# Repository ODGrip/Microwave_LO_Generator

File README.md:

# Microwave_LO_Generator
23.3 GHz - 26.3 GHz LO generator

View on CADLAB.io: https://cadlab.io/projects/microwavelogenerator

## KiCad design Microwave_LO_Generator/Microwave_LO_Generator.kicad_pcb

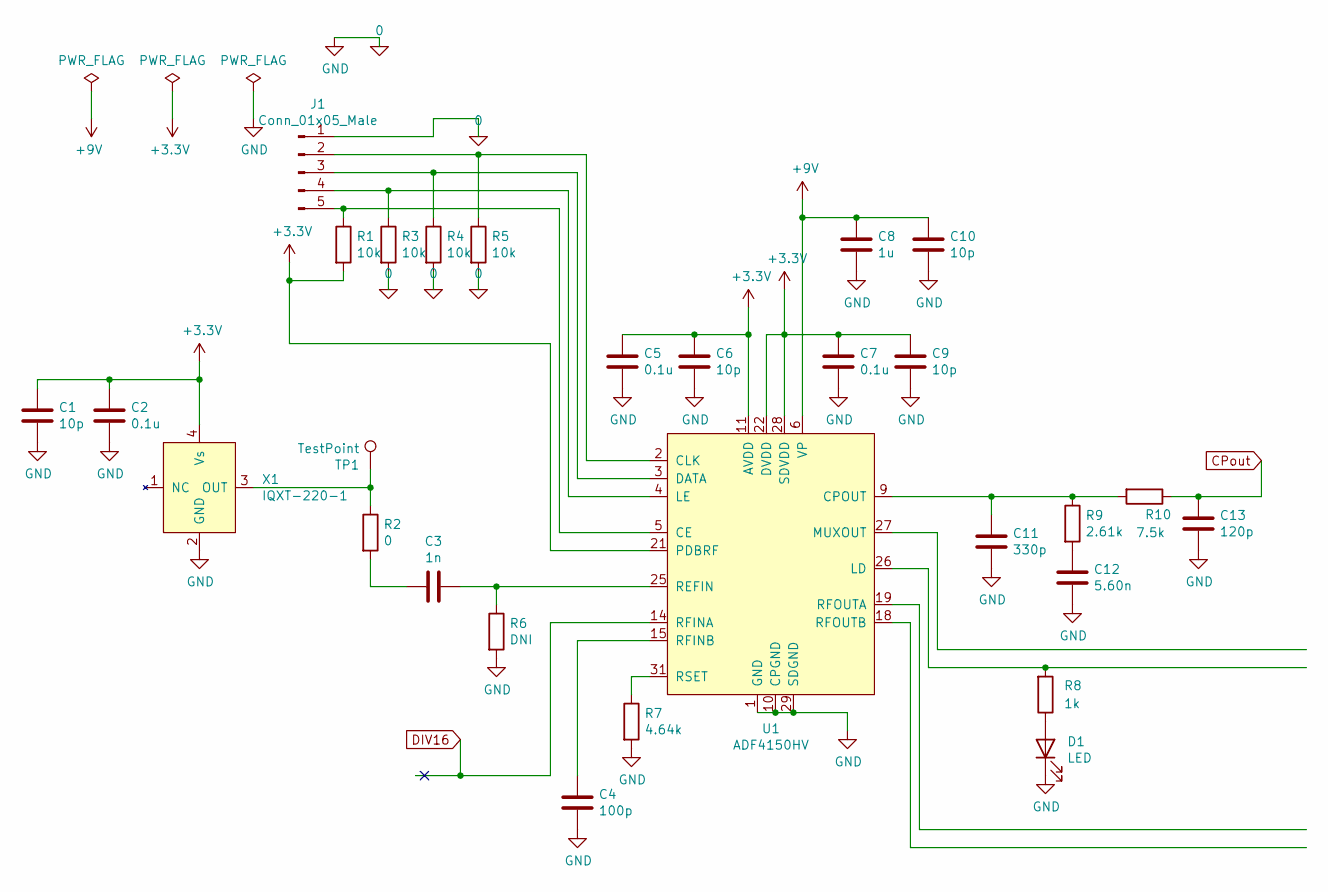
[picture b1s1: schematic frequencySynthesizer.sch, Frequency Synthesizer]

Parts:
C1, C6, C9, C10: 10p; C_0402_1005Metric_Pad0.74x0.62mm_HandSolder
C2, C5, C7: 0.1u; C_0402_1005Metric_Pad0.74x0.62mm_HandSolder
C3: 1n; C_0402_1005Metric_Pad0.74x0.62mm_HandSolder
C4: 100p; C_0402_1005Metric_Pad0.74x0.62mm_HandSolder
C8: 1u; C_0402_1005Metric_Pad0.74x0.62mm_HandSolder
C11: 330p; C_0402_1005Metric_Pad0.74x0.62mm_HandSolder
C12: 5.60n; C_0402_1005Metric_Pad0.74x0.62mm_HandSolder
C13: 120p; C_0402_1005Metric_Pad0.74x0.62mm_HandSolder
D1: LED; LED_0805_2012Metric_Pad1.15x1.40mm_HandSolder
J1: Conn_01x05_Male; PinHeader_1x05_P2.54mm_Vertical
R1, R3, R4, R5: 10k; R_0402_1005Metric_Pad0.72x0.64mm_HandSolder
R2: 0; R_0402_1005Metric_Pad0.72x0.64mm_HandSolder
R6: DNI; R_0402_1005Metric_Pad0.72x0.64mm_HandSolder
R7: 4.64k; R_0402_1005Metric_Pad0.72x0.64mm_HandSolder
R8: 1k; R_0402_1005Metric_Pad0.72x0.64mm_HandSolder
R9: 2.61k; R_0402_1005Metric_Pad0.72x0.64mm_HandSolder
R10: 7.5k; R_0402_1005Metric_Pad0.72x0.64mm_HandSolder
TP1: TestPoint; TestPoint_Loop_D2.60mm_Drill1.6mm_Beaded
U1: ADF4150HV; LFCSP-32-1EP_5x5mm_P0.5mm_mod
X1: IQXT-220-1; Oscillator_SMD_Abracon_ASE-4Pin_3.2x2.5mm_HandSoldering

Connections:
0: C1.1, C2.1, C4.1, C5.1, C6.1, C7.1, C8.1, C9.1, C10.1, C11.1, C12.1, C13.1, D1.1 (K), J1.1, R3.2, R4.2, R5.2, R6.2, R7.2, U1.1 (GND), U1.7 (GND), U1.8 (GND), U1.10 (CPGND), U1.12 (GND), U1.16 (GND), U1.17 (GND), U1.23 (GND), U1.24 (GND), U1.29 (SDGND), U1.30 (GND), U1.32 (GND), X1.2 (GND); also elsewhere on the board
+3V3: C1.2, C2.2, C5.2, C6.2, C7.2, C9.2, R1.2, U1.11 (AVDD), U1.13 (AVDD), U1.20 (AVDD), U1.21 (PDBRF), U1.22 (DVDD), U1.28 (SDVDD), X1.4 (Vs); also elsewhere on the board
+9V: C8.2, C10.2, U1.6 (VP); also elsewhere on the board
CPout: C13.2, R10.1; also elsewhere on the board
DIV16: U1.14 (RFINA); also elsewhere on the board
unnamed: C3.1, R6.1, U1.25 (REFIN)
unnamed: C3.2, R2.2
unnamed: C4.2, U1.15 (RFINB)
unnamed: C11.2, R9.1, R10.2, U1.9 (CPOUT)
unnamed: C12.2, R9.2
unnamed: D1.2 (A), R8.1
unnamed: J1.2, R5.1, U1.2 (CLK)
unnamed: J1.3, R4.1, U1.3 (DATA)
unnamed: J1.4, R3.1, U1.4 (LE)
unnamed: J1.5, R1.1, U1.5 (CE)
unnamed: R2.1, TP1.1, X1.3 (OUT)
unnamed: R7.1, U1.31 (RSET)
unnamed: R8.2, U1.26 (LD)

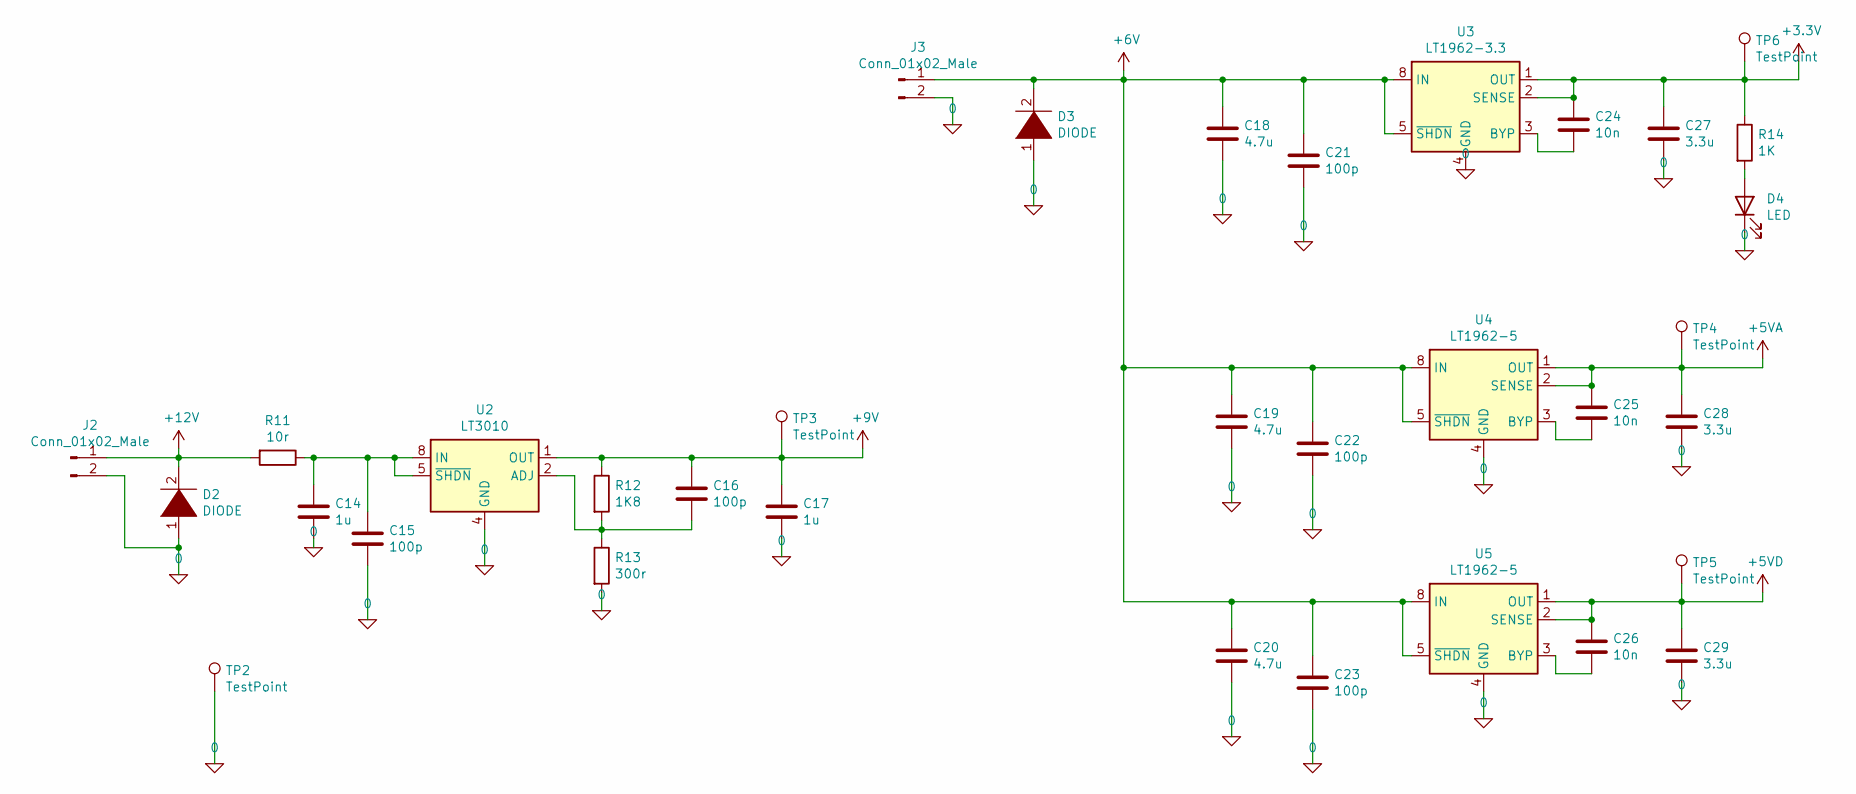
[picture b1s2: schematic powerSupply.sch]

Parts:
C14, C17: 1u; C_0402_1005Metric_Pad0.74x0.62mm_HandSolder
C15, C16, C21, C22, C23: 100p; C_0402_1005Metric_Pad0.74x0.62mm_HandSolder
C18, C19, C20: 4.7u; C_0402_1005Metric_Pad0.74x0.62mm_HandSolder
C24, C25, C26: 10n; C_0402_1005Metric_Pad0.74x0.62mm_HandSolder
C27, C28, C29: 3.3u; C_0402_1005Metric_Pad0.74x0.62mm_HandSolder
D2, D3: DIODE; D_MELF
D4: LED; LED_0805_2012Metric_Pad1.15x1.40mm_HandSolder
J2, J3: Conn_01x02_Male; PinHeader_1x02_P2.54mm_Vertical
R11: 10r; R_0402_1005Metric_Pad0.72x0.64mm_HandSolder
R12: 1K8; R_0402_1005Metric_Pad0.72x0.64mm_HandSolder
R13: 300r; R_0402_1005Metric_Pad0.72x0.64mm_HandSolder
R14: 1K; R_0402_1005Metric_Pad0.72x0.64mm_HandSolder
TP2, TP3, TP4, TP5, TP6: TestPoint; TestPoint_Loop_D2.60mm_Drill1.6mm_Beaded
U2: LT3010; MSOP-8-1EP_3x3mm_P0.65mm_EP1.68x1.88mm
U3: LT1962-3.3; MSOP-8_3x3mm_P0.65mm
U4, U5: LT1962-5; MSOP-8_3x3mm_P0.65mm

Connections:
0: C14.1, C15.1, C17.1, C18.1, C19.1, C20.1, C21.1, C22.1, C23.1, C27.1, C28.1, C29.1, D2.1 (K), D3.1 (K), D4.1 (K), J2.2, J3.2, R13.2, TP2.1, U2.4 (GND), U2.9 (GND), U3.4 (GND), U4.4 (GND), U5.4 (GND); also elsewhere on the board
+3V3: C24.2, C27.2, R14.1, TP6.1, U3.1 (OUT), U3.2 (SENSE); also elsewhere on the board
+5VA: C25.2, C28.2, TP4.1, U4.1 (OUT), U4.2 (SENSE); also elsewhere on the board
+5VD: C26.2, C29.2, TP5.1, U5.1 (OUT), U5.2 (SENSE); also elsewhere on the board
+6V: C18.2, C19.2, C20.2, C21.2, C22.2, C23.2, D3.2 (A), J3.1, U3.5 (~SHDN), U3.8 (IN), U4.5 (~SHDN), U4.8 (IN), U5.5 (~SHDN), U5.8 (IN)
+9V: C16.2, C17.2, R12.1, TP3.1, U2.1 (OUT); also elsewhere on the board
+12V: D2.2 (A), J2.1, R11.2
unnamed: C14.2, C15.2, R11.1, U2.5 (~SHDN), U2.8 (IN)
unnamed: C16.1, R12.2, R13.1, U2.2 (ADJ)
unnamed: C24.1, U3.3 (BYP)
unnamed: C25.1, U4.3 (BYP)
unnamed: C26.1, U5.3 (BYP)
unnamed: D4.2 (A), R14.2

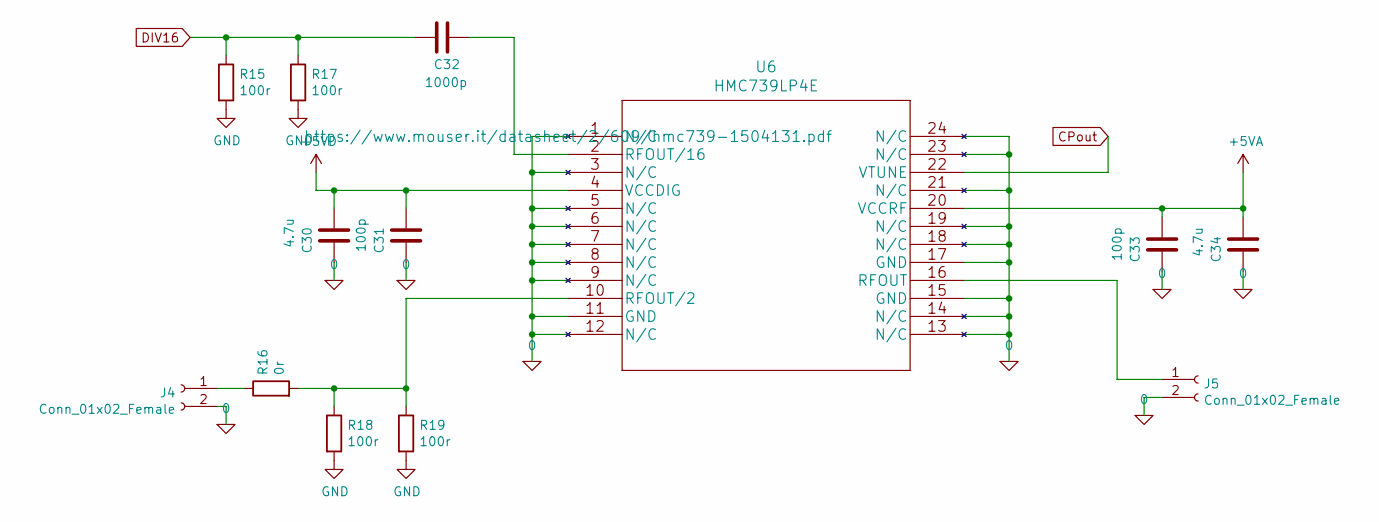
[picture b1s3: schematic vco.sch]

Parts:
C30, C34: 4.7u; C_0402_1005Metric_Pad0.74x0.62mm_HandSolder
C31, C33: 100p; C_0402_1005Metric_Pad0.74x0.62mm_HandSolder
C32: 1000p; C_0201_0603Metric_Pad0.64x0.40mm_HandSolder
J4, J5: Conn_01x02_Female; Connettore_largo
R15, R17, R18, R19: 100r; R_0201_0603_HandSolder_mod
R16: 0r; R_0201_0603_HandSolder_mod
U6: HMC739LP4E; QFN-24-1EP_4x4mm_P0.5mm_EP2.7x2.7mm_ThermalVias_mod

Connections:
0: C30.2, C31.2, C33.2, C34.2, J4.2, J5.2, R15.2, R17.2, R18.2, R19.2, U6.1 (N/C), U6.3 (N/C), U6.5 (N/C), U6.6 (N/C), U6.7 (N/C), U6.8 (N/C), U6.9 (N/C), U6.11 (GND), U6.12 (N/C), U6.13 (N/C), U6.14 (N/C), U6.15 (GND), U6.17 (GND), U6.18 (N/C), U6.19 (N/C), U6.21 (N/C), U6.23 (N/C), U6.24 (N/C); also elsewhere on the board
+5VA: C33.1, C34.1, U6.20 (VCCRF); also elsewhere on the board
+5VD: C30.1, C31.1, U6.4 (VCCDIG); also elsewhere on the board
CPout: U6.22 (VTUNE); also elsewhere on the board
DIV16: C32.1, R15.1, R17.1; also elsewhere on the board
unnamed: C32.2, U6.2 (RFOUT/16)
unnamed: J4.1, R16.1
unnamed: J5.1, U6.16 (RFOUT)
unnamed: R16.2, R18.1, R19.1, U6.10 (RFOUT/2)

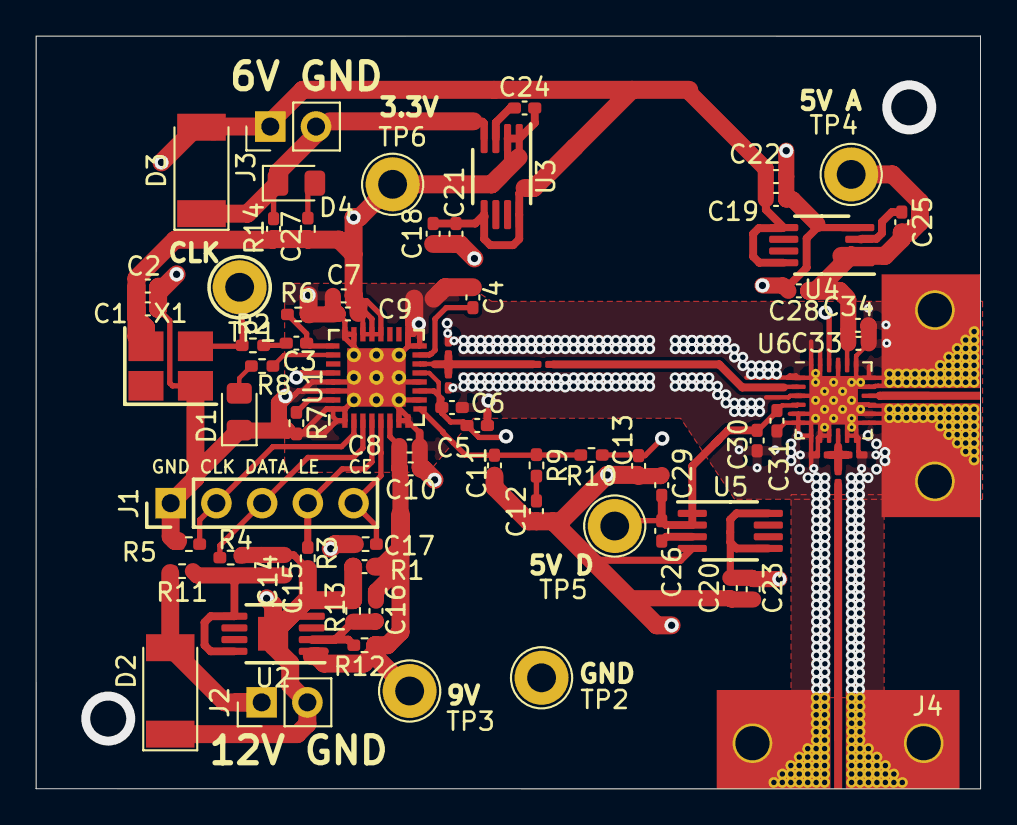
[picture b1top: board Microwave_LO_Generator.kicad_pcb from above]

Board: 4 copper layers, 52.5 x 41.8 mm, 75 parts (0 on the bottom side), 32 nets.

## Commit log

2020-11-24 First commit
    Initial setup
2020-11-25 add vco
2020-11-25 Update and fix
2020-11-25 add CADLAB.io link
2020-11-26 Update PCB
2020-11-27 Add connector pcb model
2020-12-03 Power Supply update
2020-12-04 Add RF/2
2020-12-05 A lot of change
2020-12-07 silkscreen
2020-12-07 ADD GND test probe
2020-12-12 test
2020-12-16 Add stability hole
2020-12-16 Edit annular ring
2021-01-02 Remove PullDown PDBRF
2021-01-04 some_update
2021-01-08 backup
2021-01-08 update bom
2021-01-15 solder clearence + gerber
2021-01-15 Change PCB thickness
2021-01-16 Update for DRC
